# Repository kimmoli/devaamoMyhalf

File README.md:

devaamoMyhalf
=============

Myhalf edition for Devaamo

V1.10 Original design based on kimmoli Myhalf

V1.20 SMD connector added, pogopads relocated and resized to 2 mm dia, flash hole relocated

*V1.20 Shared at OSHPark https://oshpark.com/shared_projects/6TWMNB35*

Added stl files for clips, 0.8mm and 1.6mm PCB thicknesses.

See also http://talk.maemo.org/showthread.php?t=92329

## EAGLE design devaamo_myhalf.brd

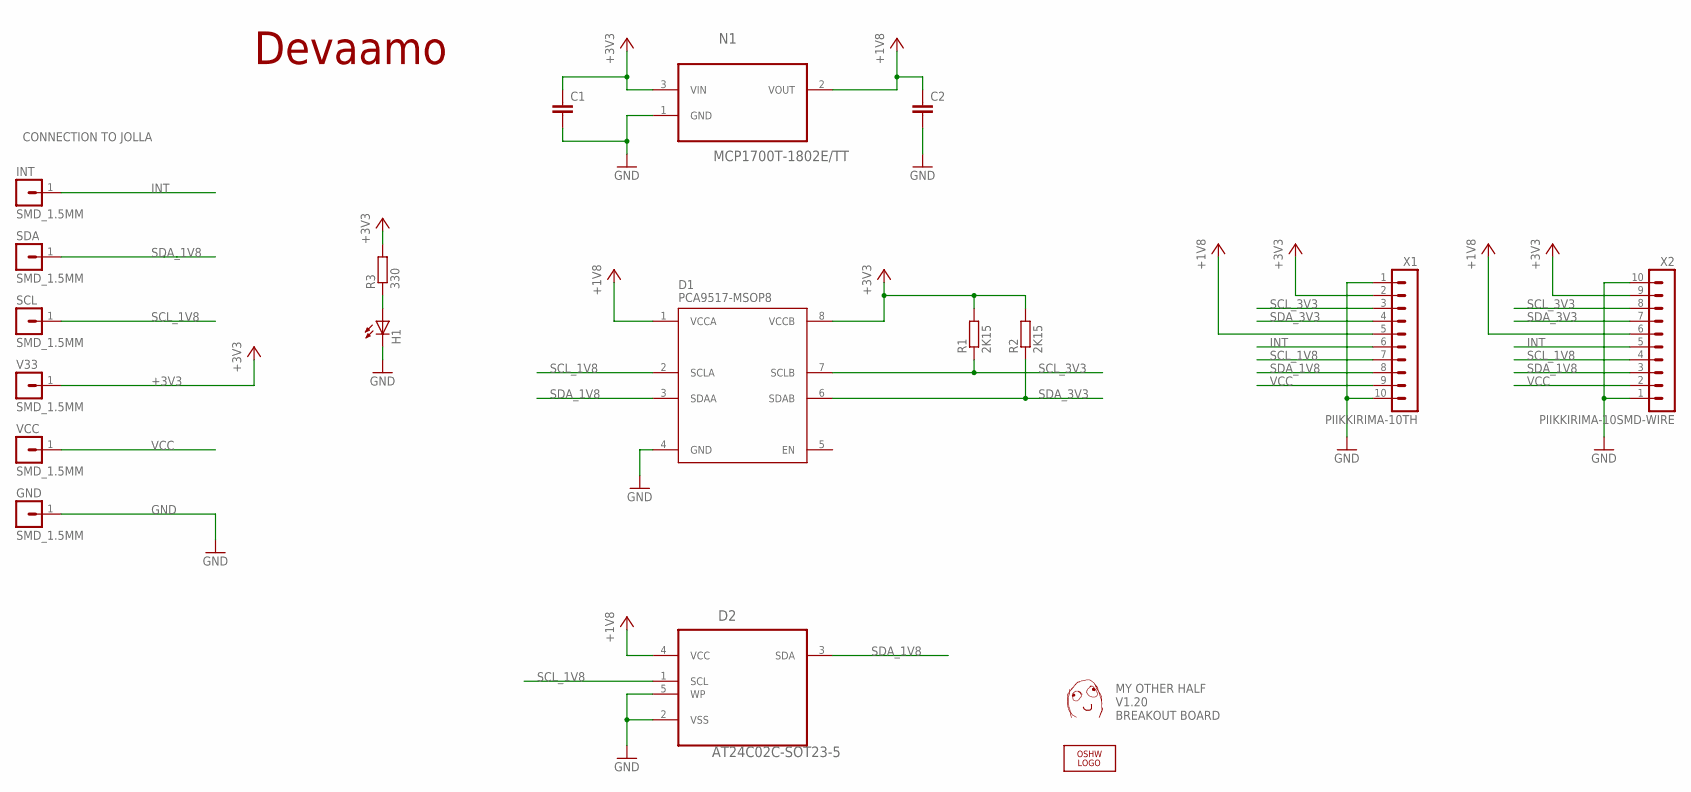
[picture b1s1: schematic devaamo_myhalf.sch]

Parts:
C1, C2: C-EUC0603; C0603
D1: PCA9517-MSOP8; SOP65P490X110-8N
D2: AT24C02C-SOT23-5; SOT95P280X145-5N
GND: SMD_1.5MM; SMD_ROUND_1.5MM
H1: LEDCHIP-LED0603; CHIP-LED0603
INT: SMD_1.5MM; SMD_ROUND_1.5MM
LOGO1: OSHW_LOGO_FILLX0200-NT; OSHW_FILLX200_NOTEXT
N1: MCP1700T-1802E/TT; SOT95P237X112-3N
R1, R2: 2K15; R0603
R3: 330; R0603
SCL: SMD_1.5MM; SMD_ROUND_1.5MM
SDA: SMD_1.5MM; SMD_ROUND_1.5MM
U$1: DAFUG
U$3: DEVAAMO
V33: SMD_1.5MM; SMD_ROUND_1.5MM
VCC: SMD_1.5MM; SMD_ROUND_1.5MM
X1: PIIKKIRIMA-10TH; PIIKKIRIMA-10
X2: PIIKKIRIMA-10SMD-WIRE; 61001018321

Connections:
+1V8: C2.1, D1.1 (VCCA), D2.4 (VCC), N1.2 (VOUT), X1.5, X2.6 (5)
+3V3: C1.1, D1.8 (VCCB), N1.3 (VIN), R1.2, R2.2, R3.2, V33.1, X1.2, X2.9 (2)
GND: C1.2, C2.2, D1.4 (GND), D2.2 (VSS), D2.5 (WP), GND.1, H1.C, N1.1 (GND), X1.1, X1.10, X2.1 (10), X2.10 (1)
INT: INT.1, X1.6, X2.5 (6)
unnamed: H1.A, R3.1
SCL_1V8: D1.2 (SCLA), D2.1 (SCL), SCL.1, X1.7, X2.4 (7)
SCL_3V3: D1.7 (SCLB), R1.1, X1.3, X2.8 (3)
SDA_1V8: D1.3 (SDAA), D2.3 (SDA), SDA.1, X1.8, X2.3 (8)
SDA_3V3: D1.6 (SDAB), R2.1, X1.4, X2.7 (4)
VCC: VCC.1, X1.9, X2.2 (9)

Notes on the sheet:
MY OTHER HALF V1.20 BREAKOUT BOARD
CONNECTION TO JOLLA

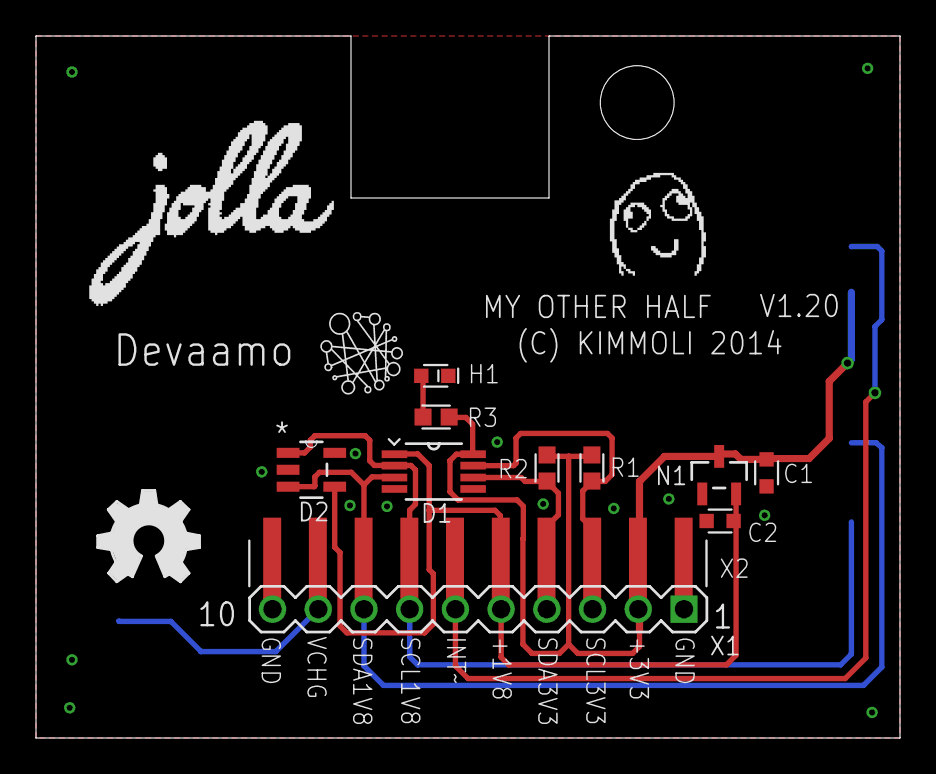
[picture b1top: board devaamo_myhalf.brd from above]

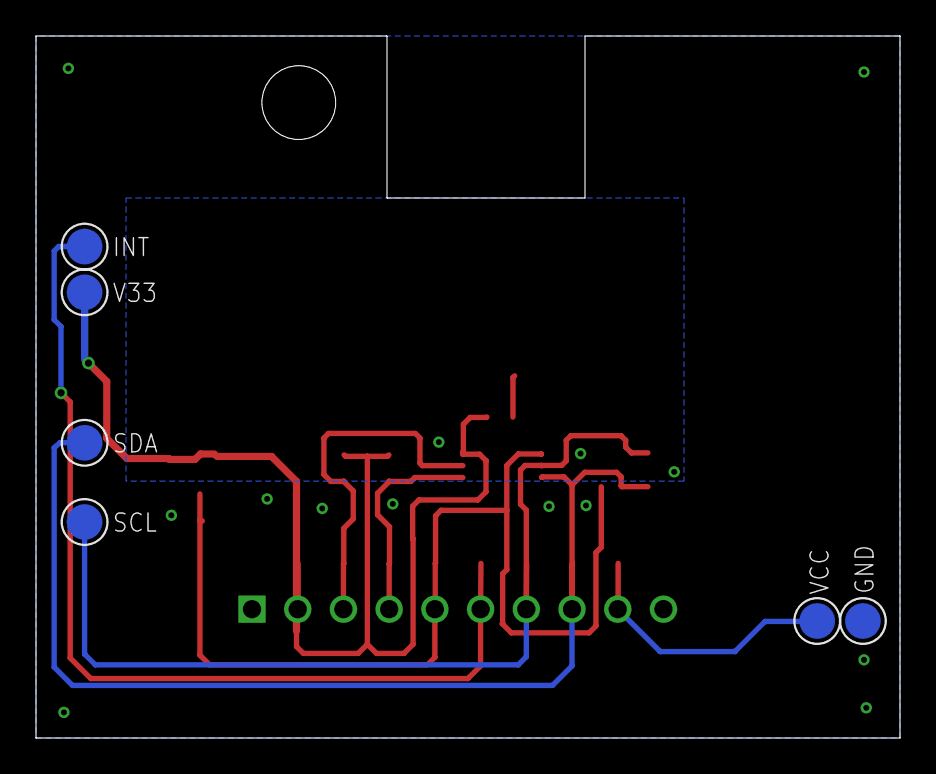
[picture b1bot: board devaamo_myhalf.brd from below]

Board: 2 copper layers, 48.0 x 39.0 mm, 21 parts (6 on the bottom side), 10 nets.

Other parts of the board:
U$2: JOLLALOGO

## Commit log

2014-03-12 V1.10 Original Devaamo Edition
2014-03-12 smd connector add, relocate flash hole, resize pogopads to 2mm
2014-03-12 gerber pdf added
2014-03-12 oshw logo added
2014-03-15 Update BOM.md
    tableish
2014-03-21 add PDF schematic
2014-03-21 Fix link
2014-07-11 stl files added
2015-01-01 rev2 0.8mm clip
